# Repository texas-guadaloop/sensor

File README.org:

* WE GO SUPER HARD WITH THEM SENSORS BOI
** Accelerometer
   The accelerometer used for the pod is the PCB 3711B112G from piezotronics
** Laser
   The laser used is the Keyence ~~~pls fill in later~~~
** Microcontrollers
   For prototyping, we are using the Arduino Uno board
   For release we are using the TM4C microcontroller

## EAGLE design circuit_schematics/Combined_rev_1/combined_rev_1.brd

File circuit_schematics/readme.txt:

Directory for circuit schematics and boards

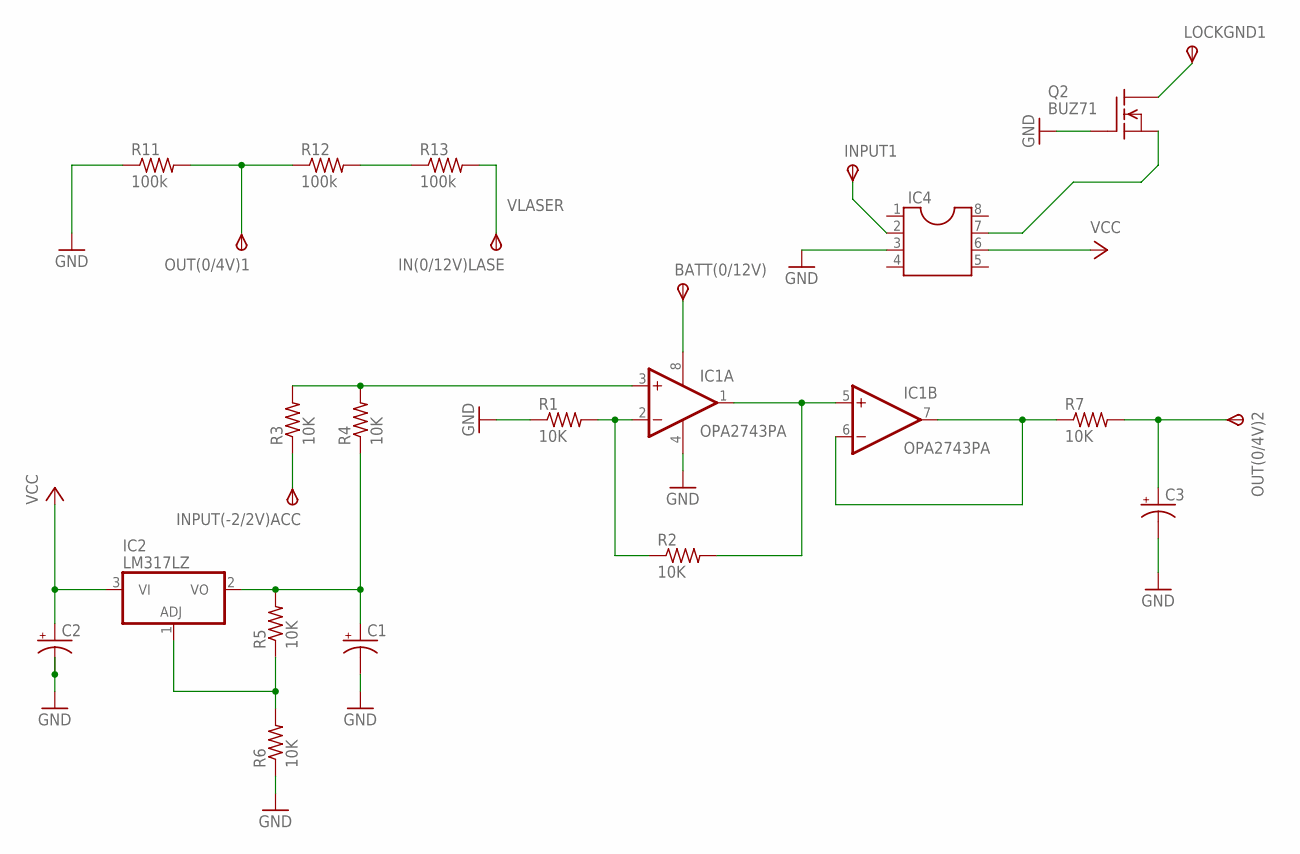
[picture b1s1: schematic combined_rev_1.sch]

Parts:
BATT(0/12V): TPSB1,27; B1,27
C1, C2, C3: CPOL-USE3.5-10; E3,5-10
IC1: OPA2743PA; DIL08
IC2: LM317LZ; TO92
IC4: DIL8S; SOCKET-08
IN(0/12V)LASE: TPSPAD1-13; P1-13
INPUT1: TPSPAD1-13; P1-13
INPUT(-2/2V)ACC: TPSPAD1-13; P1-13
LOCKGND1: TPSPAD1-13; P1-13
OUT(0/4V)1, OUT(0/4V)2: TPSB1,27; B1,27
Q2: BUZ71; TO220
R1, R2, R3, R4, R5, R6, R7: 10K; 0204/7
R11, R12, R13: 100k; V234/12

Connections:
GND: C1.-, C2.-, C3.-, IC1.4 (V-), IC4.3, Q2.1 (G), R1.1, R6.1, R11.1
unnamed: IC1.1 (OUT), IC1.5 (+IN), R2.2
unnamed: IC1.3 (+IN), R3.2, R4.2
unnamed: IC1.2 (-IN), R1.2, R2.1
unnamed: C3.+, OUT(0/4V)2.TP, R7.2
unnamed: C1.+, IC2.2 (VO), R4.1, R5.2
unnamed: IC2.1 (ADJ), R5.1, R6.2
unnamed: IC1.6 (-IN), IC1.7 (OUT), R7.1
unnamed: INPUT(-2/2V)ACC.TP, R3.1
unnamed: IC4.2, INPUT1.TP
unnamed: IC4.7, Q2.3 (S)
unnamed: LOCKGND1.TP, Q2.2 (D)
unnamed: OUT(0/4V)1.TP, R11.2, R12.1
unnamed: R12.2, R13.1
VCC: BATT(0/12V).TP, C2.+, IC1.8 (V+), IC2.3 (VI), IC4.6
VLASER: IN(0/12V)LASE.TP, R13.2

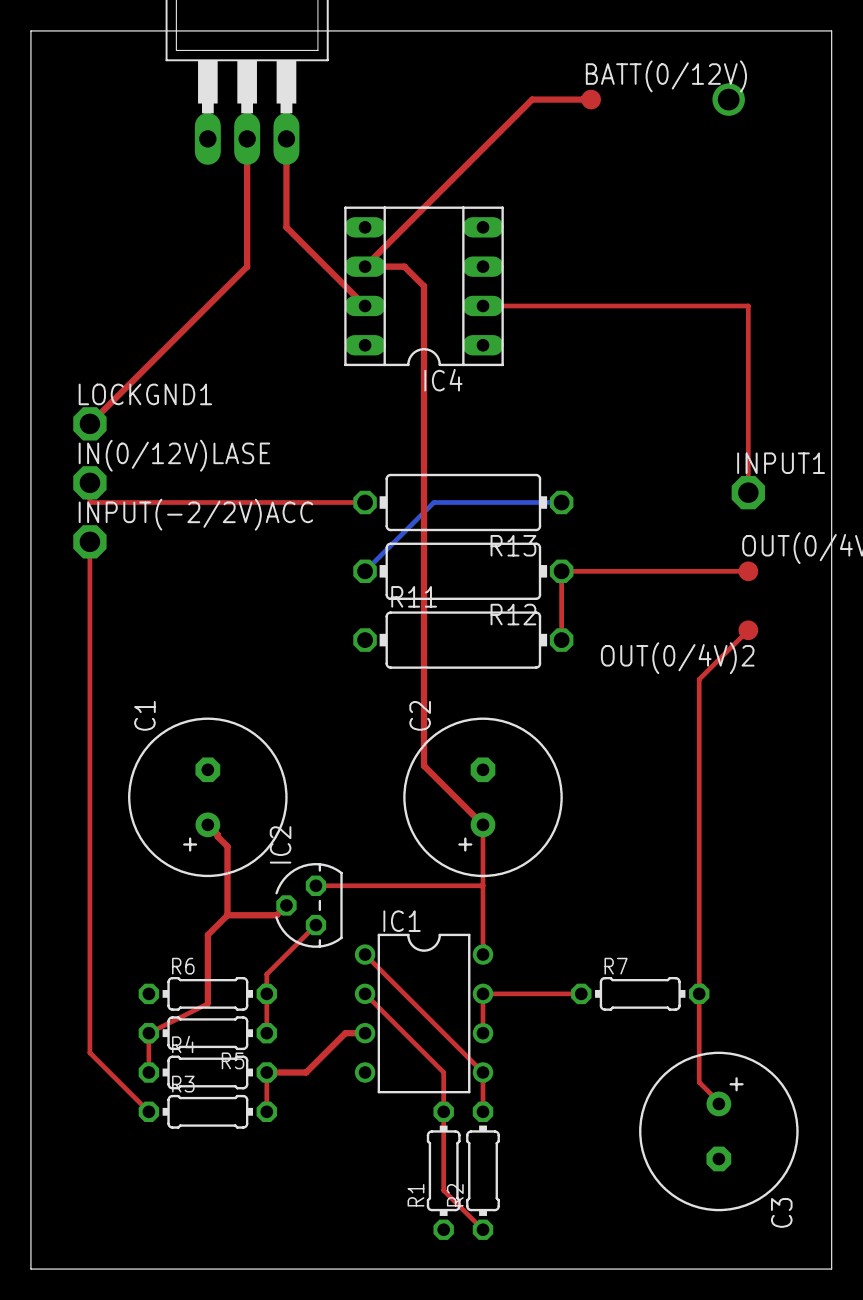
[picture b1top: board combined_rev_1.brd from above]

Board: 2 copper layers, 51.7 x 80.0 mm, 24 parts (0 on the bottom side), 16 nets.

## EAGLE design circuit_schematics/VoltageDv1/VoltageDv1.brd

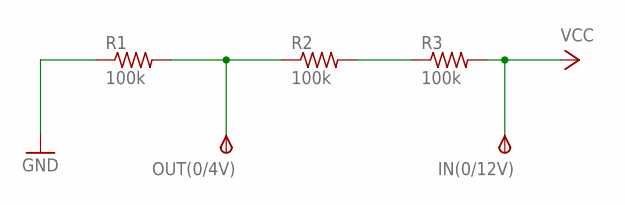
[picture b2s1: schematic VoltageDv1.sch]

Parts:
IN(0/12V): TPSB1,27; B1,27
OUT(0/4V): TPSB1,27; B1,27
R1, R2, R3: 100k; V234/12

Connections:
GND: R1.1
unnamed: OUT(0/4V).TP, R1.2, R2.1
unnamed: R2.2, R3.1
VCC: IN(0/12V).TP, R3.2

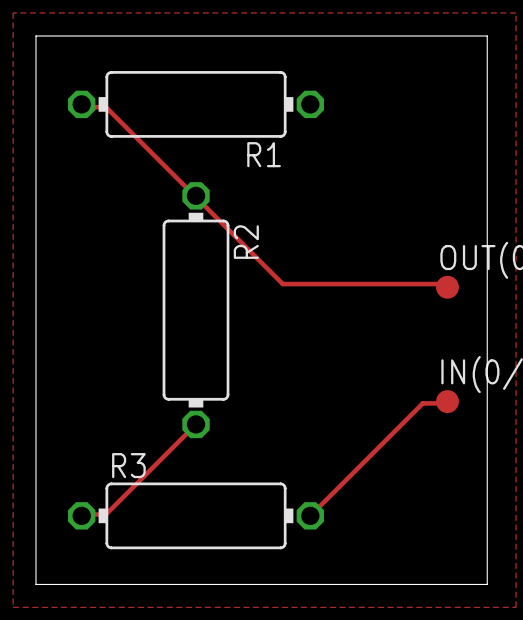
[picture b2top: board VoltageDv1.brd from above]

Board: 2 copper layers, 25.1 x 30.5 mm, 5 parts (0 on the bottom side), 3 nets.

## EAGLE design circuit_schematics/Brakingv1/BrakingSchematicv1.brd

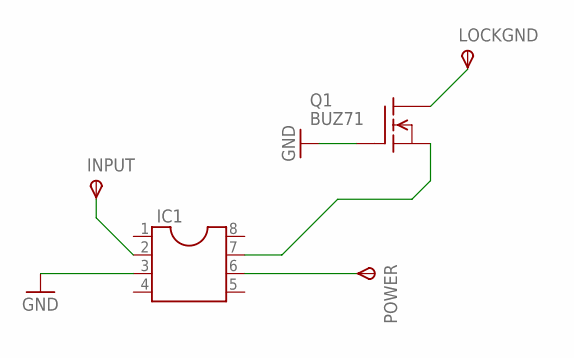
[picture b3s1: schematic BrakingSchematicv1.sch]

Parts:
IC1: DIL8S; SOCKET-08
INPUT: TPSPAD1-13; P1-13
LOCKGND: TPSPAD1-13; P1-13
POWER: TPSPAD1-13; P1-13
Q1: BUZ71; TO220

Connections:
GND: IC1.3, Q1.1 (G)
unnamed: IC1.2, INPUT.TP
unnamed: IC1.6, POWER.TP
unnamed: LOCKGND.TP, Q1.2 (D)
unnamed: IC1.7, Q1.3 (S)

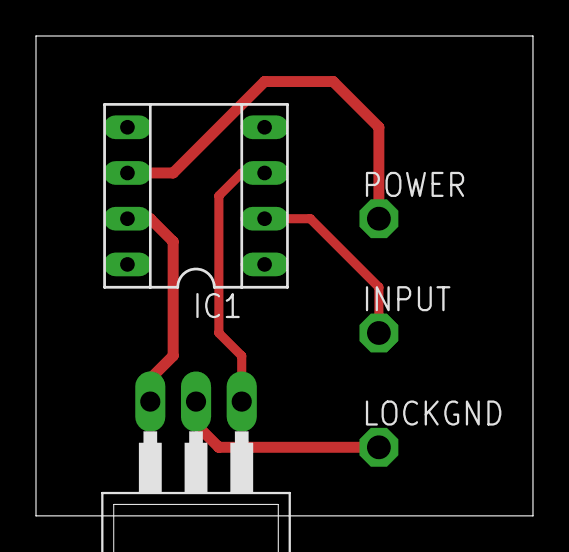
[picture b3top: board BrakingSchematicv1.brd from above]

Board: 2 copper layers, 27.6 x 26.7 mm, 5 parts (0 on the bottom side), 5 nets.

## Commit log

2016-06-10 added the README
2016-06-21 adding circuit scheme folder
2016-06-21 adding accel circuit schematic
2016-06-22 sup bois, I added voltage divider/braking circuits (Schematics & Boards)
2016-06-23 put everything so far onto one board, power connection is bad
2016-06-23 added some notes about circuits'
2016-06-23 routed the combined circuit
2016-07-12 added pressure transducer
2016-07-12 actually put the schematic, added notes
2016-07-12 same as above
2016-07-12 miscommit
2016-07-12 finished a simple high side reader
